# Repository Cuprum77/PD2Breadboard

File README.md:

# WORK IN PROGRESS - PD2Breadboard
Introducing the ultimate USB Power Delivery (PD) negotiator with unparalleled power measuring capabilities, powered by the cutting-edge RP2040 microcontroller. This isn't just any negotiator – it's a powerful variable power supply that's perfect for powering your breadboard projects on the fly, with an onboard high-resolution graphical LCD and three-button interface for easy control.

Our RP2040 powered USB PD negotiator is the perfect solution for anyone looking for a versatile, on-the-go power supply for their breadboard projects. With its advanced negotiating algorithm, this negotiator ensures optimal power delivery to your projects, while its onboard power measuring capabilities provide detailed insights into your device's power consumption.

The onboard high-resolution graphical LCD and three-button interface make it easy to control and monitor your device's power usage. With the graphical LCD, you can quickly view your device's power consumption and adjust the voltage levels to your desired level with the three-button interface.

Whether you're prototyping a new project, experimenting with electronics, or just need a reliable power source for your breadboard, our negotiator has you covered. It's capable of delivering up to 100W of power, with adjustable voltage levels ranging from 3.3V to 20V, making it compatible with a wide range of projects and devices.

And with its onboard power measuring capabilities, you'll have unprecedented insights into your device's power consumption. This feature is especially useful for those looking to optimize their device's power usage, or for those who want to monitor the power consumption of their projects in real-time.

Our RP2040 powered USB PD negotiator is also incredibly easy to use. Simply plug it into your USB port, set the voltage to your desired level using the graphical LCD and three-button interface, and let it power your breadboard project with ease. And with its compact, lightweight design, you can take it with you anywhere you go.

So why settle for a limited, fixed power supply when you can have the ultimate USB PD negotiator with onboard power measuring capabilities, variable voltage levels, and an onboard high-resolution graphical LCD and three-button interface? Take your breadboard projects to the next level!

## Technical Specifications
- RP2040 microcontroller
- 3.3V to 21V adjustable voltage levels[^1]
- 100W maximum power output[^2]
- 1.47" high-resolution graphical LCD
- 3-button interface
- USB Type-C connector
- Serial interface

[^1]: Requires a PPS capable device. The voltage levels are dependent on the power supply's capabilities.
[^2]: The maximum power output is dependent on the power supply's capabilities.

## Structure
### [Hardware](Hardware/)
The hardware folder contains all the hardware files for the project. This includes the schematic, PCB layout, and the BOM.
### [Resources](Resources/)
The resources folder contains all the resources for the project. This includes the datasheets, the user manuals, and the application notes. As well as images and other files that are used in the documentation.
### [Software/Embedded](Software/Embedded/)
The Folder contains all the software files for the microcontroller. This includes the source code, the libraries, and the relevant documentation.
### [Software/PC](Software/PC/)
The folder contains all the software files for the PC control program. This includes the source code, the libraries, and the relevant documentation.

## License
### Hardware
This hardware is licensed under the CERN Open Hardware Licence v2 - see the [LICENSE](Hardware/Rev%201/LICENSE) file for details
### Software
This software is licensed under the MIT License - see the [LICENSE](Software/Embedded/LICENSE) file for details

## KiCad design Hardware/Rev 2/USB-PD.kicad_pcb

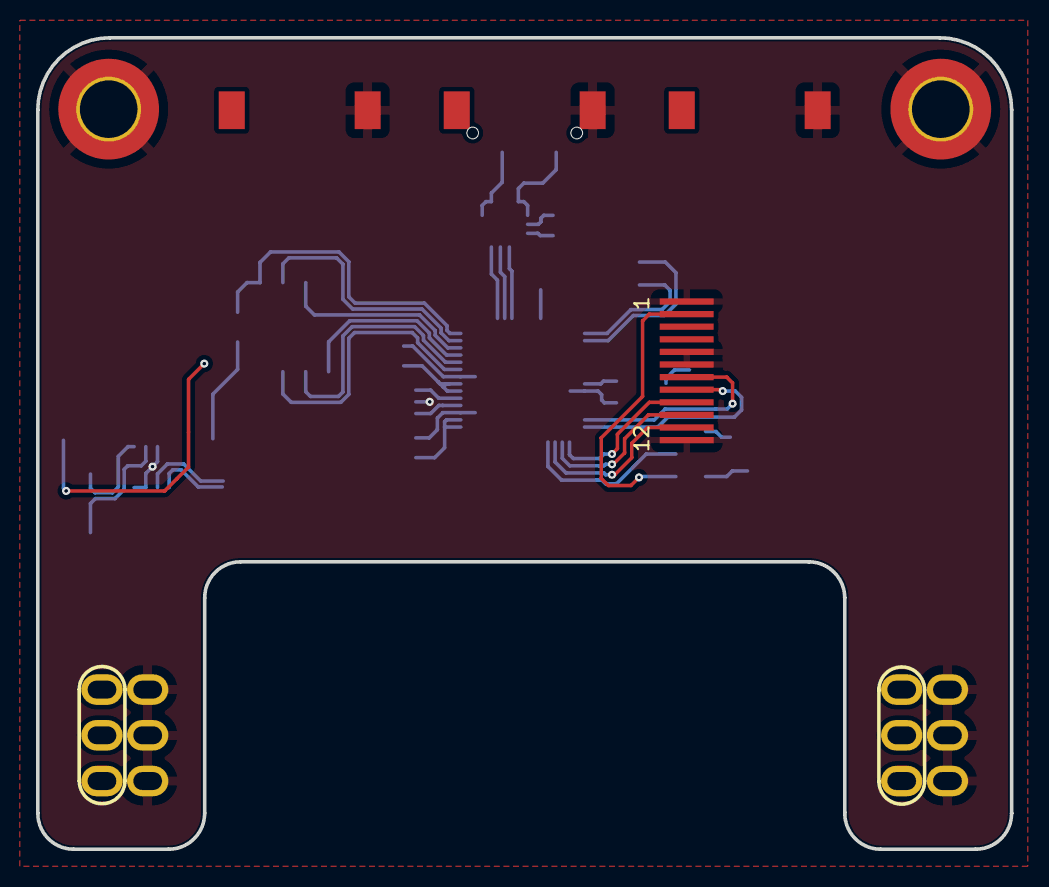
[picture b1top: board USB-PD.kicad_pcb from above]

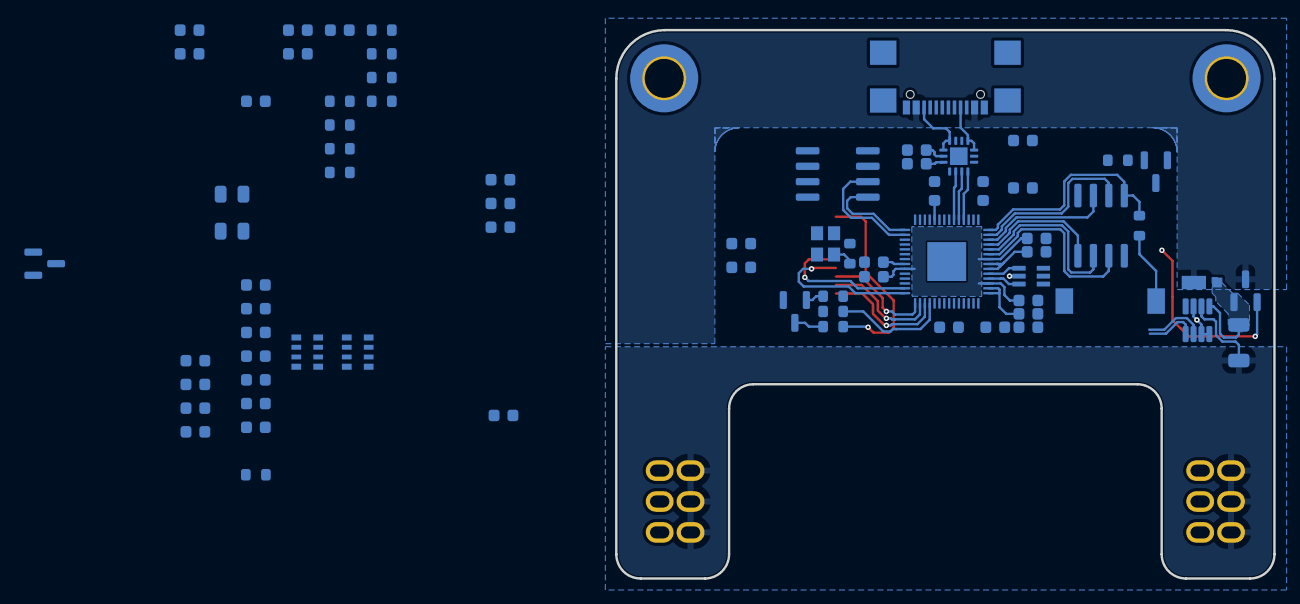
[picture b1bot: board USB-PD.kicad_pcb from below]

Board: 2 copper layers, 54.1 x 45.1 mm, 80 parts (72 on the bottom side), 49 nets.

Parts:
C1, C6, C23, C28, C35: 1u; C_0603_1608Metric
C2, C5, C8, C9, C10, C13, C14, C15, C16, C22, C24, C29, C31, C32, C33, C34, C37: 100n; C_0603_1608Metric
C3, C4, C17, C20, C26, C27: 2u2; C_0603_1608Metric
C7, C12: 330p; C_0603_1608Metric
C11: 10u; C_0603_1608Metric
C18, C19, C21: RC_C; C_0603_1608Metric
C25, C30: 100p; C_0603_1608Metric
C38, C39: 8p; C_0603_1608Metric
D1, D2: Pink; D_0805_2012Metric
D3: V1PM10HM3/H; V1PM10HM3H
DS1: ST7789_IPS_1.47; 1.47 inch 12PIN ST7789
H1, H2: M3; MountingHole_3.2mm_M3_DIN965_Pad_TopBottom
IC1: MCP1792T; SOT-23
J1: USB4110-GF-A_REVB; GCT_USB4110-GF-A_REVB
J2: R 2.54 mm; PinHeader_2x03_P2.54mm_Vertical_Elongated
J3: L 2.54 mm; PinHeader_2x03_P2.54mm_Vertical_Elongated
Q1: PMOS; SOT-23
Q2: BC817; SOT-23
Q3: BC317; SOT-23
R1, R4, R9, R10, R12, R13, R15: 1k; R_0603_1608Metric
R2, R16: DNF; R_0603_1608Metric
R3, R14: 270; R_0603_1608Metric
R5, R8: 10k; R_0603_1608Metric
R6: 100; R_0603_1608Metric
R7: 60; R_0603_1608Metric
R17: 10m; R_1206_3216Metric
RN1, RN2: 10k; R_Array_Convex_4x0603
SW1: SW_MENU; PTS636 SM25J SMTR LFS
SW2: SW_DOWN; PTS636 SM25J SMTR LFS
SW3: SW_CONF; PTS636 SM25J SMTR LFS
SW4: DNF; PTS636 SM25J SMTR LFS
U1: FUSB302BMPX; WQFN-14-1EP_2.5x2.5mm_P0.5mm_EP1.45x1.45mm
U2: RP2040; QFN-56-1EP_7x7mm_P0.4mm_EP3.2x3.2mm
U3: FT24C04A; SOIC-8_3.9x4.9mm_P1.27mm
U4: INA219AxDCN; SOT-23-8
U5: USBUF02W6; SOT65P210X110-6N
U6: W25Q16JV; SOIC-8_3.9x4.9mm_P1.27mm
Y1: 12MHz; Crystal_SMD_2520-4Pin_2.5x2.0mm

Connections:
+1V1: C6.1, C8.1, C10.1, U2.23 (DVDD), U2.45 (VREG_VOUT), U2.50 (DVDD)
+3V3: C1.1, C2.1, C5.1, C13.1, C14.1, C15.1, C16.1, C17.1, C20.1, C22.1, C31.1, C32.1, C33.1, C34.1, C35.1, C37.1, DS1.3 (LEDA), DS1.4 (VDD), IC1.2, R1.2, R2.2, R5.2, R9.2, R10.2, R12.2, R13.2, RN2.5 (R4.2), RN2.6 (R3.2), RN2.7 (R2.2), U1.3 (VDD), U1.4 (VDD), U1.12 (VCONN), U1.13 (VCONN), U2.1 (IOVDD), U2.10 (IOVDD), U2.22 (IOVDD), U2.33 (IOVDD), U2.42 (IOVDD), U2.43 (ADC_AVDD), U2.44 (VREG_IN), U2.48 (USB_VDD), U2.49 (IOVDD), U3.8 (VCC), U4.4 (VS), U5.5 (3V3), U6.8 (VCC)
/CC1: C7.1, J1.A5 (CC1), U1.10 (CC1), U1.11 (CC1)
/CC2: C12.1, J1.B5 (CC2), U1.1 (CC2), U1.14 (CC2)
/Display/BL_CTR: DS1.2 (LEDK), R7.1
/I2C0_SCL: R13.1, U2.16 (GPIO13), U3.6 (SCL), U4.5 (SCL)
/I2C0_SDA: R12.1, U2.15 (GPIO12), U3.5 (SDA), U4.6 (SDA)
/LCD_BL: R4.1, U2.32 (GPIO21)
/LCD_CS: DS1.8 (CS), U2.28 (GPIO17)
/LCD_D/C: DS1.7 (D/C), U2.27 (GPIO16)
/LCD_MOSI: DS1.10 (SDA), U2.30 (GPIO19)
/LCD_RST: DS1.11 (RESET), U2.31 (GPIO20)
/LCD_SCK: DS1.9 (SCL), U2.29 (GPIO18)
/MOSFETs/POW_OUT: C23.1, C24.1, C25.1, C28.1, C29.1, C30.1, J2.1, J2.3, J2.5, J3.1, J3.3, J3.5, R17.2, U4.2 (IN-)
/PD_INT_N: R1.1, U1.5 (INT_N), U2.6 (GPIO4)
/PD_SCL: R10.1, U1.6 (SCL), U2.5 (GPIO3)
/PD_SDA: R9.1, U1.7 (SDA), U2.4 (GPIO2)
/RMOS: R6.1, U2.36 (GPIO24)
/RP2040/LED_LMOS: R14.2, U2.18 (GPIO15)
/RP2040/LED_RMOS: R3.2, U2.37 (GPIO25)
/RP2040/QSPI_SCLK: U2.52 (QSPI_SCLK), U6.6 (CLK)
/RP2040/QSPI_SD0: U2.53 (QSPI_SD0), U6.5 (DI(IO0))
/RP2040/QSPI_SD1: U2.55 (QSPI_SD1), U6.2 (DO(IO1))
/RP2040/QSPI_SD2: U2.54 (QSPI_SD2), U6.3 (IO2)
/RP2040/QSPI_SD3: U2.51 (QSPI_SD3), U6.7 (IO3)
/RP2040/QSPI_SS: R2.1, R16.1, U2.56 (QSPI_SS), U6.1 (~CS)
/RP2040/XIN: C39.2, U2.20 (XIN), Y1.1
/RP2040/XOUT: R15.1, U2.21 (XOUT)
/SW1: RN1.1 (R1.1), U2.14 (GPIO11)
/SW2: RN1.2 (R2.1), U2.13 (GPIO10)
/SW3: RN1.3 (R3.1), U2.12 (GPIO9)
/USB/USB_PRE_D+: J1.A6 (D+), J1.B6 (D+), U5.6 (D+)
/USB/USB_PRE_D-: J1.A7 (D-), J1.B7 (D-), U5.4 (D-)
/USB_D+: U2.47 (USB_DP), U5.1 (D+)
/USB_D-: U2.46 (USB_DM), U5.3 (D-)
GND: C1.2, C2.2, C3.2, C4.2, C5.2, C6.2, C7.2, C8.2, C9.2, C10.2, C11.2, C12.2, C13.2, C14.2, C15.2, C16.2, C17.2, C18.2, C19.2, C20.2, C21.2, C22.2, C23.2, C24.2, C25.2, C26.2, C27.2, C28.2, C29.2, C30.2, C31.2, C32.2, C33.2, C34.2, C35.2, C37.2, C38.1, C39.1, D1.1 (K), D2.1 (K), DS1.1 (GND), DS1.5 (GND), DS1.6 (GND), DS1.12 (GND), H1.1, H2.1, IC1.1, J1.A1/B12 (GND), J1.B1/A12 (GND), J1.S1 (SHIELD), J1.S2 (SHIELD), J1.S3 (SHIELD), J1.S4 (SHIELD), J2.2, J2.4, J2.6, J3.2, J3.4, J3.6, Q2.2 (E), Q3.1 (E), SW1.2, SW2.2, SW3.2, SW4.1, U1.8 (GND), U1.9 (GND), U1.15 (GND), U2.57 (GND), U3.1 (A0), U3.2 (A1), U3.3 (A3), U3.4 (GND), U3.7 (WP), U4.3 (GND), U4.7 (A0), U4.8 (A1), U5.2 (Grd), U6.4 (GND), Y1.2, Y1.4
unnamed: C38.2, R15.2, Y1.3
unnamed: D1.2 (A), R3.1
unnamed: D2.2 (A), R14.1
unnamed: D3.2 (A), Q1.1 (D), R17.1, U4.1 (IN+)
unnamed: Q1.2 (G), Q3.3 (C), R8.2
unnamed: Q2.1 (B), R4.2, R5.1
unnamed: Q2.3 (C), R7.2
unnamed: Q3.2 (B), R6.2
unnamed: R16.2, SW4.2
unnamed: C18.1, RN1.8 (R1.2), RN2.4 (R4.1), SW1.1
unnamed: C19.1, RN1.7 (R2.2), RN2.3 (R3.1), SW2.1
unnamed: C21.1, RN1.6 (R3.2), RN2.2 (R2.1), SW3.1
VBUS: C3.1, C4.1, C9.1, C11.1, C26.1, C27.1, D3.1 (K), IC1.3, J1.A4/B9 (VBUS), J1.B4/A9 (VBUS), Q1.3 (S), R8.1, U1.2 (VBUS)

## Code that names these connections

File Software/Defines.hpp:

// This is a header guard. It prevents the file from being included more than once.
#pragma once

/***
 *      ____  _           
 *     |  _ \(_)_ __  ___ 
 *     | |_) | | '_ \/ __|
 *     |  __/| | | | \__ \
 *     |_|   |_|_| |_|___/
 *                        
 */

// I2C bus that the EEPROM and INA219 are connected to
#define I2C0_SDA            12
#define I2C0_SCL            13

// I2C bus that the FUSB302 is connected to
#define I2C1_SDA            2
#define I2C1_SCL            3
#define PD_INT_N            4

// Display pins
#define DISP_PIN_DC         16
#define DISP_PIN_CS         17
#define DISP_PIN_SCK        18
#define DISP_PIN_MOSI       19
#define DISP_PIN_RST        20
#define DISP_PIN_BL         21

// Button pins
#define BUTTON_UP           9
#define BUTTON_MENU         10
#define BUTTON_DOWN         11

// Mosfet pins and LEDs
#define LEFT_MOSFET_LED     15
#define LEFT_MOSFET         14
#define RIGHT_MOSFET_LED    25
#define RIGHT_MOSFET        24



/***
 *     __     __         _       _     _           
 *     \ \   / /_ _ _ __(_) __ _| |__ | | ___  ___ 
 *      \ \ / / _` | '__| |/ _` | '_ \| |/ _ \/ __|
 *       \ V / (_| | |  | | (_| | |_) | |  __/\__ \
 *        \_/ \__,_|_|  |_|\__,_|_.__/|_|\___||___/
 *                                                 
 */

// Display constants
#define DISP_WIDTH          172     // 172 pixels wide
#define DISP_HEIGHT         320     // 320 pixels tall
#define DISP_OFFSET_X0      34      // cut off on the left side of the display
#define DISP_OFFSET_X1      34      // cut off on the right side of the display
#define DISP_OFFSET_Y0      0       // cut off on the top of the display
#define DISP_OFFSET_Y1      0       // ut off on the bottom of the display
#define DISP_ROTATION       0       // 0, 1, 2, or 3

// I2C constants
#define I2C0_SPEED          1000000  // 1 MHz
#define I2C1_SPEED          1000000  // 1 MHz

// System constants
#define MULTICORE_FLAG_VALUE        0x69

// default values
#define CURRENT_LIMIT_DEFAULT       3000    // mA
#define CURRENT_SETTING_DEFAULT     1000    // mA
#define VOLTAGE_SETTING_DEFAULT     5000    // mV
#define BACKLIGHT_DEFAULT           255     // 0-255
#define VOLTAGE_STEPS               20      // USB PPS voltage steps in mV
#define CURRENT_STEPS               50      // USB PPS current steps in mA

// serial interface codes
#define REBOOT_TO_BOOTLOADER_CODE   "reboot_to_bootloader"
#define RESET_CODE                  "reset"
#define GET_SETTINGS_CODE           "get_settings"

// INA219 codes
#define CURRENT_LIMIT_CODE          "current_limit:"
#define CURRENT_SETTING_CODE        "current_setting:"
#define VOLTAGE_SETTING_CODE        "voltage_setting:"
#define GET_READINGS_CODE           "get_readings"
#define GET_READINGS_RAW_CODE       "get_readings_raw"

// FUSB302 codes
#define FUSB302_DUMP_DATA           "dump_usb"
#define FUSB302_GET_IDENTITY        "get_identity"
#define FUSB302_GET_CAPABILITY      "get_capability"

// display codes
#define BACKLIGHT_CODE              "backlight:"

// general peripheral codes
#define TEST_CODE                   "test"



/***
 *         _       _     _                             
 *        / \   __| | __| |_ __ ___  ___ ___  ___  ___ 
 *       / _ \ / _` |/ _` | '__/ _ \/ __/ __|/ _ \/ __|
 *      / ___ \ (_| | (_| | | |  __/\__ \__ \  __/\__ \
 *     /_/   \_\__,_|\__,_|_|  \___||___/___/\___||___/
 *                                                     
 */

#define FUSB302_ADDRESS     0x22
#define INA219_ADDRESS      0x40
#define EEPROM_ADDRESS      0x50


/***
 *      ___            _           _           
 *     |_ _|_ __   ___| |_   _  __| | ___  ___ 
 *      | || '_ \ / __| | | | |/ _` |/ _ \/ __|
 *      | || | | | (__| | |_| | (_| |  __/\__ \
 *     |___|_| |_|\___|_|\__,_|\__,_|\___||___/
 *                                             
 */

#include <stdio.h>
#include "pico/stdlib.h"
#include "pico/bootrom.h"
#include "pico/binary_info.h"
#include "pico/multicore.h"
#include "hardware/uart.h"
#include "hardware/i2c.h"
#include "hardware/watchdog.h"
#include "tusb.h"

#include "Button.hpp"
#include "Display.hpp"
#include "USB_PD.hpp"
#include "INA219.hpp"
#include "Memory.hpp"
#include "Background.h"



/***
 *      ____  _         _____           _    ____        _        
 *     |  _ \(_) ___ __|_   _|__   ___ | |  |  _ \  __ _| |_ __ _ 
 *     | |_) | |/ __/ _ \| |/ _ \ / _ \| |  | | | |/ _` | __/ _` |
 *     |  __/| | (_| (_) | | (_) | (_) | |  | |_| | (_| | || (_| |
 *     |_|   |_|\___\___/|_|\___/ \___/|_|  |____/ \__,_|\__\__,_|
 *                                                               
 */

bi_decl(bi_program_name("USB-PD Power Supply"));
bi_decl(bi_program_description("Your own USB-PD variable power supply with an active circuit breaker."));
bi_decl(bi_program_version_string("1.0.0"));
bi_decl(bi_program_url("https://github.com/Cuprum77/PD2Breadboard"));

bi_decl(bi_4pins_with_names(DISP_PIN_CS, "SPI Chip Select", DISP_PIN_SCK, "SPI Clock", DISP_PIN_MOSI, "SPI Data", DISP_PIN_RST, "SPI Reset"));
bi_decl(bi_2pins_with_names(DISP_PIN_DC, "SPI Data Control", DISP_PIN_BL, "Display Backlight"));
bi_decl(bi_3pins_with_names(BUTTON_UP, "Button Up", BUTTON_MENU, "Button Menu", BUTTON_DOWN, "Button Down"));
bi_decl(bi_1pin_with_name(PD_INT_N, "USB-PD Interrupt"));

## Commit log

2023-04-09 early display gfx
2023-04-09 script update
2023-04-09 basic gfx
2023-04-09 rename to fix case issue
2023-04-09 Linux fixes thanks to https://github.com/diminDDL
2023-04-09 improved on color struct
2023-04-09 improvement on structs
2023-04-09 missing font file
2023-04-10 added bitmap support, and its faster than adafruit
2023-04-12 cleanup
2023-04-12 font update
2023-04-16 automatic programming on build
2023-04-17 font update, scaling, colors and easier usage
2023-04-17 simplification
2023-04-17 added vital piss color
2023-04-17 minor changes
2023-04-17 more characters and numbers supported
2023-04-17 fixed float rounding error
2023-04-17 optimization
2023-04-17 multicore
2023-04-21 forgot to keep track of the polling time
2023-04-24 beep
2023-04-26 abstraction part of driver complete
2023-04-26 gitignore and ibom update
2023-04-26 name conflict resolved
2023-04-26 fixed cmake to allow include
2023-04-26 abstracted the writing of registers
2023-04-26 self test capabilities
2023-04-26 syntax errors
2023-04-26 reorder
2023-05-03 PCB specific changes
2023-05-03 USB PD updates
2023-05-03 boolean support
2023-05-07 i have no idea what im doing
2023-05-09 restructuring
2023-05-09 rev 2
2023-05-09 added PD specs
2023-05-09 loicense
2023-05-09 git hash capabilities
2023-05-09 restructure pt2
2023-05-09 typo
2023-05-09 removing build in favor of github actions
2023-05-09 skill issue moment
2023-05-09 hopefully this fixes the github actions issues
2023-05-09 skill issue part 2
2023-05-10 i need to debloat this in the future
2023-05-10 minor tweaks
2023-05-10 more git stuff
2023-05-10 debloat
2023-05-10 minor changes, got basic communication
2023-05-11 removed problematic printf
2023-05-11 added registers
2023-05-11 fixes
2023-05-11 unsafe access for your unsafe needs
2023-05-11 reg handler
2023-05-12 restructure v2
2023-05-12 readme update
2023-05-12 fixed link
2023-05-19 changed to updated library
2023-05-26 gradient rotating
2023-05-30 still cant get PD to work properly ¯\_(ツ)_/¯
2023-05-30 optimized gradient rotator
2023-05-31 updated picogfx
2023-06-02 improved performance by 50%
2023-06-03 added pio
2023-06-08 started on pcb design
2023-06-08 small changes
2023-06-13 minor work
2023-06-22 smaller tweaks
2023-07-01 minor changes to account for library change
2023-07-01 background test lmao
2023-07-02 tweaks
2023-07-08 restructure part 2
2023-07-08 fixed gitmodules
2023-07-09 hopefully fixed git error from refactor
2023-07-09 untracked refactor files i think
2023-07-09 steaming update
2023-07-09 i forgor 💀
2023-07-10 something
2023-07-10 updated to match library changes
2023-08-31 removed the usb pd library as it does not work
2023-08-31 renamed defines.hpp to main.h
2023-08-31 updated cmakelists to reflect the loss of usb pd
2023-08-31 updated main to utilize the latest picogfx version
2024-01-09 remove ibom from linguist
